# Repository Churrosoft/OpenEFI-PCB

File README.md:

# OpenEFI-PCB
Coleccion de PCB y planos recomendados para montar una OpenEFI

### Sobre el proyecto
OpenEFI es un ECU/EFI programable basada en arduino, totalmente OpenSource, fue creada originalmente para reemplazar una ecu existente en un motor naftero, pero tambien se puede usar para agregar inyeccion y/o encendido electronico a un motor antiguo, cuenta tambien con soporte para DTC's y autodiagnostico
* [OpenEFI](https://github.com/FDSoftware/OpenEFI) [Repo principal con todo el codigo]
* [OpenEFI-Tuner](https://github.com/FDSoftware/OpenEFI-Tuner) [Utilidad para revisar el estado de la ecu y modificarla]
* 
### Placas soportadas
* STM32F407xxxx: uEFI (v2/v3)
* STM32F103c8t6: OpenEFI (v0.5/v1/v2)

### coautores externos:
Dibujos:
Lucacik / ig: https://www.instagram.com/luca.cik/

si quieres usar otra placa basada en Arduino (Uno, Mega,DUE,etc), puedes hacerlo, pero los pcb no te serviran y capaz tengas que modificar ligeramente el codigo y el mapeo de los pines, proximamente agregare mas pcb ademas de mejorar los existentes

This source is distributed WITHOUT ANY EXPRESS OR IMPLIED WARRANTY, INCLUDING OF MERCHANTABILITY, SATISFACTORY QUALITY AND FITNESS FOR A PARTICULAR PURPOSE.

Please see LICENSE file for applicable conditions.

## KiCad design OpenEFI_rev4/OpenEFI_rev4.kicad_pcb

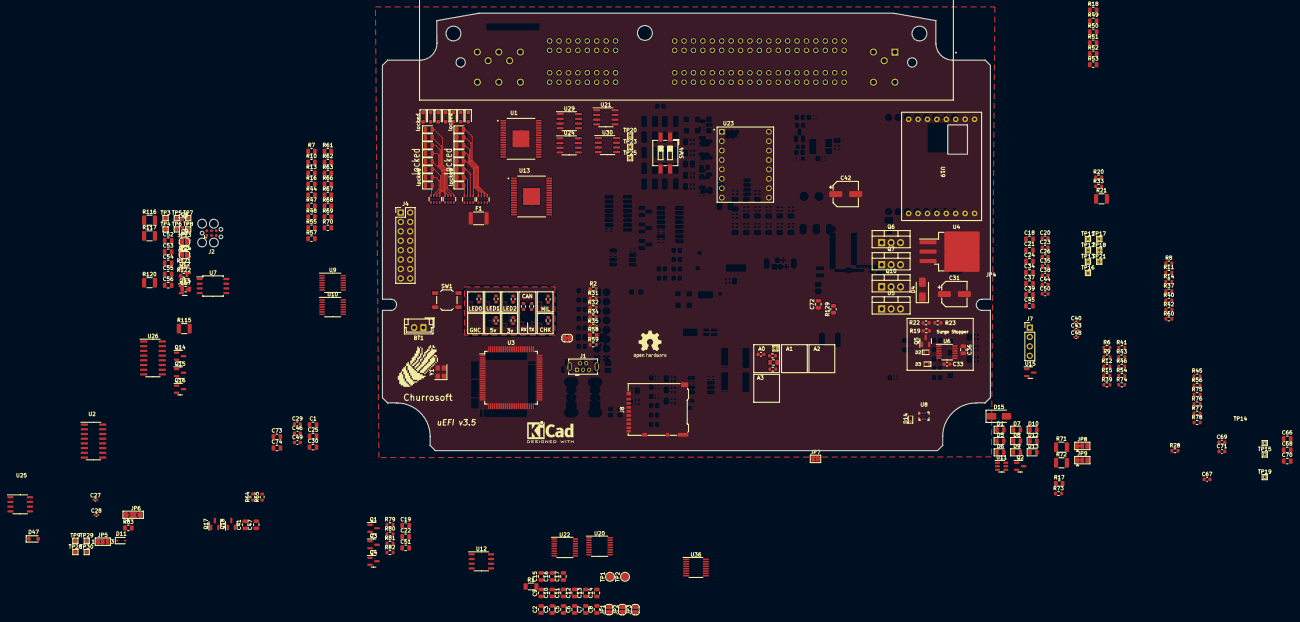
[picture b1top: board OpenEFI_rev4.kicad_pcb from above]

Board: 4 copper layers, 164.0 x 118.0 mm, 293 parts (0 on the bottom side), 205 nets.

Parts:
BT1: Battery_Cell; JST_EH_B2B-EH-A_1x02_P2.50mm_Vertical
C1, C5, C9, C10, C11, C12, C13, C14, C15, C17, C18, C21, C24, C25, C30, C32, C34, C36, C37, C39, C45, C66, C68, C70: 100nF; C_0805_2012Metric
C2, C3: 15pF; C_0805_2012Metric
C4, C20, C23, C26, C29, C35, C38, C44, C46, C49, C50, C67, C69, C71: 0.22uF; C_0603_1608Metric
C6, C73: 1uF; C_0805_2012Metric
C7, C8: 2.2uF; C_0805_2012Metric
C16: 4.7uF; C_0805_2012Metric
C19, C22, C41, C51, C52, C53, C54, C55, C56, C57, C72: 0.01uF; C_0805_2012Metric
C27, C28: 47p; C_0402_1005Metric
C31, C42: 100uF ±20% 35V; CP_Elec_6.3x7.7
C33: 47nF; C_0603_1608Metric
C40, C43: 1u; C_0402_1005Metric
C47: 4700pF; C_0805_2012Metric
C48: 100n; C_0402_1005Metric
C74: 0.1uF; C_0805_2012Metric
Churrosoft: SYM_Hot_Large; churro_new_v4
D1, D5, D6, D7, D8, D9, D10, D12, D13, D16, D17, D18, D19, D20, D21, D22, D43, D63, D65, D67, D69, D71, D73, D75, D77: LED; LED_0805_2012Metric
D2, D3: 1N4148; D_SOD-523
D4: SMAJ58CA; D_SMA
D11: MM3Z24VT1G; D_SOD-323
D14: 1N914WT; D_SOD-523
D15: SS26; D_SMA
D47, D64, D66, D68, D70, D72, D74, D76: D; D_SOD-323_HandSoldering
F1: Polyfuse; Fuse_1812_4532Metric
J1: USB_B; USB_Mini-B_Tensility_54-00023_Vertical
J2: Tag connect; Tag-Connect_TC2030-IDC-FP_2x03_P1.27mm_Vertical
J4: Conn_02x08_Odd_Even; PinHeader_2x08_P2.54mm_Vertical
J6: 1241434-1; TE_1241434-1
J7: Conn_01x04; PinHeader_1x04_P2.54mm_Vertical
J8: Micro_SD_Card_Det1; microSD_HC_Hirose_DM3AT-SF-PEJM5
JP1, JP2, JP3, JP23, JP24: SolderJumper_2_Open; SolderJumper-2_P1.3mm_Open_RoundedPad1.0x1.5mm
JP4: Jumper_NO_Small; SolderJumper-2_P1.3mm_Open_RoundedPad1.0x1.5mm
JP5: SolderJumper-3_P1.3mm_Bridged2Bar12_Pad1.0x1.5mm_NumberLabe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
JP6: SolderJumper_3_Bridged12; SolderJumper-3_P2.0mm_Open_TrianglePad1.0x1.5mm
JP7: Jumper_2_Open; SolderJumper-2_P1.3mm_Bridged2Bar_Pad1.0x1.5mm
JP8, JP9: Jumper_3_Bridged12; SolderJumper-3_P1.3mm_Bridged12_Pad1.0x1.5mm
LOGO1: Logo_Open_Hardware_Large; OSHW-Logo2_9.8x8mm_SilkScreen
Q1, Q2, Q3, Q4, Q12, Q13, Q14, Q15, Q16, Q17, Q18: AO3400A; SOT-23
Q5, Q8, Q9, Q11: SS8050; SOT-23
Q6, Q7: IRLZ44N; TO-220-3_Vertical
Q10: IRF540N; TO-220-3_Vertical
R1: 120R; R_1206_3216Metric
R2, R59, R121, R122: 10k; R_0603_1608Metric
R3, R4, R5, R24, R25, R26, R27, R29, R30: 4.7k; R_0603_1608Metric
R6, R9, R12, R15, R36, R39, R41, R43, R46, R54, R74: 2.49k +-1%; R_0603_1608Metric
R7, R44, R48, R61, R63, R66, R69, R70: 348k; R_0805_2012Metric
R8, R11, R14, R37, R38, R40, R42, R45, R56, R60, R75, R76, R77, R78: 470R; R_0603_1608Metric
R10, R13, R47, R55, R57, R62, R67, R68: 180k; R_0805_2012Metric
R16: 604R; R_0805_2012Metric
R17, R18, R49, R50, R51, R52, R53, R58, R83, R129: 10k; R_0805_2012Metric
R19: 1M 1/10W; R_0603_1608Metric
R20, R33, R73: 10R 1/10W; R_0603_1608Metric
R21: 0.01R; R_1210_3225Metric
R22: 57.6K 1/10W; R_0603_1608Metric
R23: 4.99K 1/10W; R_0603_1608Metric
R28: 3.88k; R_0603_1608Metric
R31, R32, R34, R64, R65, R79, R80, R81, R82: 1k; R_0603_1608Metric
R35: 100k; R_0603_1608Metric
R71, R72, R116, R117: 10K 1/2W; R_1210_3225Metric
R115, R120: 4.99K 1/2W; R_1210_3225Metric
RN1, RN2, RN3, RN4: 1k; R_Array_Convex_4x0603
SW1: SW_Push; SW_SPST_TL3342
SW4: SW_DIP_x02; SW_DIP_SPSTx02_Slide_6.7x6.64mm_W8.61mm_P2.54mm_LowProfile
SYM1: SYM_Hot_Small; KiCad-Logo2_5mm_SilkScreen
TP1: BOOT0; TestPoint_Pad_D2.0mm
TP2: BOOT1; TestPoint_Pad_D2.0mm
TP3, TP4, TP5, TP6, TP7, TP8, TP9, TP28, TP29, TP30: TestPoint; TestPoint_Pad_1.0x1.0mm
TP10, TP11, TP12, TP13, TP14, TP15, TP16, TP17, TP18, TP19, TP20, TP21, TP23, TP25: TestPoint_Alt; TestPoint_THTPad_1.0x1.0mm_Drill0.5mm
U1, U13: MCZ33810EK; SOP65P1030X245-33N
U2: 74HC4851; SOIC-16_3.9x9.9mm_P1.27mm
U3: STM32F407VGTx; LQFP-100_14x14mm_P0.5mm
U4: MIC2940A-3.3WU; TO-263-3_TabPin2
U5: MIC2940A-5.0WT; TO-220-3_Vertical
U6: LT4363IMS; MSOP-12_3x4mm_P0.65mm
U7: 25LCxxx; SOIC-8_5.275x5.275mm_P1.27mm
U8: BMP280; Bosch_LGA-8_2x2.5mm_P0.65mm_ClockwisePinNumbering
U9, U10: LMV324; TSSOP-14_4.4x5mm_P0.65mm
U11: SRV05-4; SOT-23-6
U12, U25: TJA1051T-3; SOP-8_3.9x4.9mm_P1.27mm
U15: REF3033; SOT-23
U19: f042_wideband_module; rusEFI_WBO
U20, U22: TPL7407LAPWR; TSSOP-16_4.4x5mm_P0.65mm
U21, U24, U29, U30: TC4424A; SOIC-8_3.9x4.9mm_P1.27mm
U23: PaP_Driver_v1; MODULE_A4988_STEPPER_MOTOR_DRIVER_CARRIER
U26: SP720ABTG; SOP-16_3.9x9.9mm_P1.27mm
U36: MAX9926UAEE+; QSOP-16_3.9x4.9mm_P0.635mm
Y1: 25MHz; Crystal_SMD_3225-4Pin_3.2x2.5mm

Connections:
5V_ENABLE: R33.1, U3.16 (PC1)
+3V3: C5.1, C6.1, C10.1, C11.1, C12.1, C13.1, C14.1, C15.1, C16.1, C17.1, C31.1, D1.2 (A), D5.2 (A), D7.2 (A), D8.2 (A), D9.2 (A), D10.2 (A), D12.2 (A), D13.2 (A), D14.2 (A), J2.1, J4.1, JP1.1 (A), JP2.1 (A), JP3.1 (A), JP5.2 (C), Q1.1 (G), Q2.1 (G), Q3.1 (G), Q4.1 (G), Q14.1 (G), Q15.1 (G), Q16.1 (G), Q17.1 (G), Q18.1 (G), R49.2, R51.2, R53.2, R59.1, R64.1, R65.1, R79.2, R80.2, R81.2, R82.2, R121.1, R122.1, U1.8 (VDD), U3.11 (VDD), U3.19 (VDD), U3.21 (VREF+), U3.28 (VDD), U3.50 (VDD), U3.75 (VDD), U3.100 (VDD), U4.3 (OUT), U7.3 (~WP), U7.7 (~HOLD), U7.8 (VCC), U8.6 (VDDIO), U8.8 (VDD), U9.4 (V+), U10.4 (V+), U12.5 (VIO), U13.8 (VDD), U23.5 (RESET), U23.6 (SLEEP), U26.16 (V+)
+5C: C40.1, D6.2 (A), D15.1 (K), F1.1, J4.2, Q10.3 (S), R6.2, R9.2, R12.2, R15.2, R18.1, R36.2, R39.2, R41.2, R43.2, R46.2, R50.1, R52.1, R54.2, R74.2, U2.16 (Vdd), U5.3 (OUT), U12.3 (VCC), U15.1 (IN), U19.1 (5V), U25.3 (VCC), U36.14 (VCC)
+12V: C42.1, JP4.2, JP6.3 (B), R21.1, R22.1, R28.2, R35.1, RN1.5 (R4.2), RN1.6 (R3.2), RN1.7 (R2.2), RN1.8 (R1.2), RN2.5 (R4.2), RN2.6 (R3.2), RN2.7 (R2.2), RN2.8 (R1.2), U1.25 (VPWR), U4.1 (IN), U5.1 (IN), U6.2 (OUT), U13.25 (VPWR), U20.9 (COM), U22.9 (COM), U23.16 (VMOT)
+12VA: D2.2 (A), JP4.1, Q5.2 (E), Q6.3 (S)
/ACC_DET: R58.1, U3.80 (PC12)
/AUX_CS_1: J4.3, U3.45 (PE14)
/AUX_CS_2: J4.5, U3.46 (PE15)
/AUX_IN_1: J4.7, U3.91 (PB5)
/AUX_IN_2: J4.9, U3.92 (PB6)
/AUX_IN_3: J4.11, U3.93 (PB7)
/AUX_IN_4: J4.13, U3.95 (PB8)
/AUX_OUT_1: J4.10, U3.33 (PC4)
/AUX_OUT_2: J4.12, U3.34 (PC5)
/AUX_OUT_3: J4.14, U3.35 (PB0)
/CHK: Q9.3 (C), R30.2
/CHK_OUT: R32.1, U3.66 (PC9), U20.6 (IN6)
/CKP: C41.1, C47.1, Q18.2 (S), R65.2, R122.2, TP7.1, U3.63 (PC6), U36.5 (COUT2)
/CKP/CMP_sensors/CKP_VR: C55.1, JP9.1 (A), R117.1
/CKP/CMP_sensors/IN1+: C54.1, R72.2, R115.1, TP4.1, U36.16 (IN1+)
/CKP/CMP_sensors/IN1-: C54.2, JP23.1 (A), R71.2, TP5.1, U36.15 (IN1-)
/CKP/CMP_sensors/IN2+: C57.2, JP24.1 (A), R117.2, TP6.1, U36.10 (IN2-)
/CKP/CMP_sensors/IN2-: C57.1, R116.2, R120.1, TP3.1, U36.9 (IN2+)
/CMP: Q17.2 (S), R64.2, R121.2, TP8.1, U3.64 (PC7), U36.4 (COUT1)
/ECN1: U1.24 (GIN0), U3.57 (PD10)
/ECN2: U1.23 (GIN1), U3.58 (PD11)
/INY1: U1.10 (DIN0), U3.55 (PD8)
/INY2: U1.11 (DIN1), U3.56 (PD9)
/LED0: R25.2, U3.7 (PC13)
/LED1: R26.2, U3.8 (PC14)
/LED2: R27.2, U3.9 (PC15)
/LED_CAN_RX: R24.2, U3.87 (PD6)
/LED_CAN_TX: R5.2, U3.88 (PD7)
/MEMORY_CS: TP9.1, U3.44 (PE13), U7.1 (~CS)
/MIL: Q8.3 (C), R29.2
/MIL_OUT: R31.1, U3.65 (PC8), U20.7 (IN7)
/MTR_DIR: U3.39 (PE8), U23.8 (DIR)
/MTR_ENABLE: U3.41 (PE10), U23.1 (ENABLE)
/MTR_FAULT: JP5.3 (B), U3.40 (PE9)
/MTR_STEP: U3.38 (PE7), U23.7 (STEP)
/MUX_A: Q16.2 (S), R49.1, U3.83 (PD2)
/MUX_B: Q14.2 (S), R51.1, U3.84 (PD3)
/MUX_C: Q15.2 (S), R53.1, U3.85 (PD4)
/NRST: C9.2, J2.3, SW1.1, U3.14 (NRST)
/PMIC1_CS: U1.4 (~CS), U3.78 (PC10)
/PMIC1_ENABLE: R83.2, R129.2, U1.9 (~OUTEN), U3.51 (PB12)
/PMIC2_CS: U3.79 (PC11), U13.4 (~CS)
/PMIC2_ENABLE: U3.52 (PB13), U13.9 (~OUTEN)
/PMIC/FB0: U1.2 (FB0), U13.2 (FB0)
/PMIC/FB1: U1.15 (FB1), U13.15 (FB1)
/PMIC/FB2: U1.31 (FB2), U13.31 (FB2)
/PMIC/FB3: U1.18 (FB3), U13.18 (FB3)
/PMIC/GD0: U1.3 (GD0), U13.3 (GD0), U21.2 (IN_A), U29.2 (IN_A)
/PMIC/GD1: U1.14 (GD1), U13.14 (GD1), U21.4 (IN_B), U29.4 (IN_B)
/PMIC/GD2: U1.30 (GD2), U13.30 (GD2), U24.2 (IN_A), U30.2 (IN_A)
/PMIC/GD3: U1.19 (GD3), U13.19 (GD3), U24.4 (IN_B), U30.4 (IN_B)
/RPM_OUT: R34.1, U3.42 (PE11)
/R_AAC: U3.3 (PE4), U22.1 (IN1), U22.2 (IN2)
/R_ECN_INY: U3.1 (PE2), U22.5 (IN5), U22.6 (IN6)
/R_GNC_GLP: U3.2 (PE3), U22.3 (IN3), U22.4 (IN4)
/R_LMB: U3.97 (PE0), U22.7 (IN7)
/SPI2_MISO: J4.6, J7.3, TP30.1, U1.7 (SO), U3.53 (PB14), U7.2 (MISO), U13.7 (SO)
/SPI2_MOSI: J4.8, J7.2, TP29.1, U1.6 (SI), U3.54 (PB15), U7.5 (MOSI), U13.6 (SI)
/SPI2_SCK: J4.4, J7.1, TP28.1, U1.5 (SCLK), U3.47 (PB10), U7.6 (SCK), U13.5 (SCLK)
/SYS_SWCLK: J2.4, U3.76 (PA14)
/SYS_SWDIO: J2.2, U3.72 (PA13)
/SYS_SWO: J2.6, U3.89 (PB3)
/Sensores/A: Q16.3 (D), R18.2, U2.11 (A)
/Sensores/AUX_CH1: C4.1, R38.1, TP10.1, U26.1 (I1)
/Sensores/AUX_CH2: C20.1, R11.1, TP11.1, U26.2 (I2)
/Sensores/AUX_CH3: C23.1, R14.1, TP12.1, U26.3 (I3)
/Sensores/AUX_CH4: C26.1, R37.1, TP13.1, U26.4 (I4)
/Sensores/AUX_CH5: C35.1, R8.1, TP16.1, U26.5 (I5)
/Sensores/AUX_CH6: C38.1, R60.1, TP17.1, U26.6 (I6)
/Sensores/AUX_CH7: C44.1, R42.1, TP18.1, U26.7 (I7)
/Sensores/AUX_CH8: C50.1, R40.1, TP21.1, U26.9 (I8)
/Sensores/B: Q14.3 (D), R50.2, U2.10 (B)
/Sensores/C: Q15.3 (D), R52.2, U2.9 (C)
/Sensores/CAN_RX: U19.5 (CAN_RX), U25.4 (RXD)
/Sensores/CAN_TX: U19.6 (CAN_TX), U25.1 (TXD)
/Sensores/CH_CLT: C69.1, R45.1, TP15.1, U26.14 (I13)
/Sensores/CH_IAT: C67.1, R47.2, R75.1, TP14.1, U26.15 (I14)
/Sensores/CH_MAP: C46.1, R13.2, R77.1, TP23.1, U26.11 (I10)
/Sensores/CH_O2: C49.1, R55.2, R78.1, TP25.1, U26.10 (I9)
/Sensores/CH_TPS: C71.1, R10.2, R76.1, TP19.1, U26.12 (I11)
/Sensores/CH_VBATT: C29.1, R56.1, R62.2, R67.2, TP20.1, U26.13 (I12)
/Sensores/LSU_Heater-: U19.11 (HEATER-), U19.12 (HEATER-)
/Sensores/mux_out: R57.2, U2.3 (OUT)
/TIM9_CH1: U3.4 (PE5), U20.1 (IN1), U20.2 (IN2), U20.3 (IN3)
/TIM9_CH2: U3.5 (PE6), U20.4 (IN4), U20.5 (IN5)
/USB_D+: J1.3 (D+), U3.71 (PA12), U11.3 (IO2)
/USB_D-: J1.2 (D-), U3.70 (PA11), U11.1 (IO1)
/VBUS: D15.2 (A), J1.1 (VBUS), U3.68 (PA9), U11.5 (VP)
A1: D11.1 (K), Q12.3 (D)
B1: C18.1, C21.1, C24.1, C32.1, C34.1, C37.1, C39.1, C45.1, R6.1, R8.2, R9.1, R11.2, R12.1, R14.2, R15.1, R36.1, R37.2, R38.2, R39.1, R40.2, R41.1, R42.2, R43.1, R60.2
B4: U20.12 (OUT5), U20.13 (OUT4)
C4: U20.14 (OUT3), U20.15 (OUT2), U20.16 (OUT1)
CAN+: C27.2, R1.2, U12.7 (CANH), U25.7 (CANH)
CAN-: C28.1, JP7.1 (A), U12.6 (CANL), U25.6 (CANL)
CKP-: C56.1, R116.1
CMP-: C52.1, R71.1
D4: U22.11 (OUT6), U22.12 (OUT5)
E1: C30.1, C66.1, C68.1, C70.1, R45.2, R46.1, R54.1, R74.1, R75.2, R76.2, R77.2
G3: U22.13 (OUT4), U22.14 (OUT3)
GND: BT1.2 (-), C1.2, C2.2, C3.2, C4.2, C5.2, C6.2, C7.2, C8.2, C9.1, C10.2, C11.2, C12.2, C13.2, C14.2, C15.2, C16.2, C17.2, C18.2, C19.1, C20.2, C21.2, C22.1, C23.2, C24.2, C25.2, C26.2, C27.1, C28.2, C29.2, C30.2, C31.2, C32.2, C33.2, C34.2, C35.2, C36.2, C37.2, C38.2, C39.2, C40.2, C42.2, C43.2, C44.2, C45.2, C46.2, C48.2, C49.2, C50.2, C51.1, C52.2, C53.2, C55.2, C56.2, C66.2, C67.2, C68.2, C69.2, C70.2, C71.2, C72.1, C73.1, C74.2, D3.2 (A), D4.2 (A2), D11.2 (A), D16.1 (K), D17.1 (K), D18.1 (K), D19.1 (K), D20.1 (K), D21.1 (K), D22.1 (K), D77.1 (K), J1.4 (GND), J1.5 (Shield), J2.5, J4.15, J4.16, J7.4, Q8.2 (E), Q9.2 (E), Q11.2 (E), Q12.2 (S), Q13.2 (S), R2.2, R3.2, R4.2, R7.2, R16.1, R23.1, R44.2, R48.2, R61.2, R63.2, R66.2, R69.2, R70.2, R83.1, R129.1, SW1.2, SW4.1, SW4.2, U1.33 (GND), U2.6 (EN), U2.8 (GND), U3.10 (VSS), U3.20 (VSSA), U3.27 (VSS), U3.74 (VSS), U3.99 (VSS), U4.2 (GND), U5.2 (GND), U6.9 (GND), U7.4 (GND), U8.1 (GND), U8.7 (GND), U9.11 (V-), U10.11 (V-), U11.2 (VN), U12.2 (GND), U12.8 (S), U13.33 (GND), U15.3 (GND), U19.2 (GND), U19.9 (HEAT_GND), U19.10 (HEAT_GND2), U20.8 (GND), U21.3 (GND), U22.8 (GND), U23.9 (GND), U23.15 (GND), U24.3 (GND), U25.2 (GND), U25.8 (S), U26.8 (GND), U29.3 (GND), U30.3 (GND), U36.1 (INT_THRS1), U36.3 (BIAS1), U36.6 (BIAS2), U36.8 (INT_THRS2), U36.11 (GND), U36.13 (ZERO_EN), Y1.2, Y1.4
H1: Q13.3 (D), R59.2
H3: U22.15 (OUT2), U22.16 (OUT1)
IGN1: RN3.8 (R1.2), U21.7 (OUT_A), U29.7 (OUT_A)
IGN2: RN3.7 (R2.2), U21.5 (OUT_B), U29.5 (OUT_B)
IGN3: RN3.5 (R4.2), U24.7 (OUT_A), U30.7 (OUT_A)
IGN4: RN3.6 (R3.2), U24.5 (OUT_B), U30.5 (OUT_B)
IGN_V+: C73.2, C74.1, JP6.2 (C), U21.6 (VDD), U24.6 (VDD), U29.6 (VDD), U30.6 (VDD)
INJ1: D47.1 (K), U1.1 (OUT0), U13.1 (OUT0)
INJ2: D64.1 (K), U1.16 (OUT1), U13.16 (OUT1)
INJ3: D66.1 (K), U1.32 (OUT2), U13.32 (OUT2)
INJ4: D68.1 (K), U1.17 (OUT3), U13.17 (OUT3)
K1: C1.1, R78.2
MCU-D23: C19.2, C22.2, C51.2, C72.2, Q1.3 (D), Q2.3 (D), Q3.3 (D), Q4.3 (D), R79.1, R80.1, R81.1, R82.1
unnamed: BT1.1 (+), D14.1 (K), U3.6 (VBAT)
unnamed: C25.1, R16.2, R28.1, R56.2
unnamed: C41.2, SW4.4
unnamed: C47.2, SW4.3
unnamed: D1.1 (K), R5.1
unnamed: D2.1 (K), Q5.1 (B), R17.2
unnamed: D3.1 (K), R17.1
unnamed: D4.1 (A1), Q6.2 (D), Q7.2 (D), U6.5 (VCC)
unnamed: D5.1 (K), R24.1
unnamed: D6.1 (K), R4.1
unnamed: D7.1 (K), R3.1
unnamed: D8.1 (K), R25.1
unnamed: D9.1 (K), R26.1
unnamed: D10.1 (K), R27.1
unnamed: D12.1 (K), R29.1
unnamed: D13.1 (K), R30.1
unnamed: D16.2 (A), RN3.2 (R2.1)
unnamed: D17.2 (A), RN3.3 (R3.1)
unnamed: D18.2 (A), RN3.4 (R4.1)
unnamed: D19.2 (A), RN4.1 (R1.1)
unnamed: D20.2 (A), RN4.2 (R2.1)
unnamed: D21.2 (A), RN4.3 (R3.1)
unnamed: D22.2 (A), RN4.4 (R4.1)
unnamed: D43.2 (A), RN1.1 (R1.1)
unnamed: D43.1 (K), D47.2 (A)
unnamed: D63.2 (A), RN1.2 (R2.1)
unnamed: D63.1 (K), D64.2 (A)
unnamed: D65.2 (A), RN1.3 (R3.1)
unnamed: D65.1 (K), D66.2 (A)
unnamed: D67.2 (A), RN1.4 (R4.1)
unnamed: D67.1 (K), D68.2 (A)
unnamed: D69.2 (A), RN2.1 (R1.1)
unnamed: D69.1 (K), D70.2 (A)
unnamed: D71.2 (A), RN2.2 (R2.1)
unnamed: D71.1 (K), D72.2 (A)
unnamed: D73.2 (A), RN2.3 (R3.1)
unnamed: D73.1 (K), D74.2 (A)
unnamed: D75.2 (A), RN2.4 (R4.1)
unnamed: D75.1 (K), D76.2 (A)
unnamed: D77.2 (A), RN3.1 (R1.1)
unnamed: JP1.2 (B), U23.3 (M1)
unnamed: JP2.2 (B), U23.2 (M0)
unnamed: JP3.2 (B), U23.4 (M2)
unnamed: JP5.1 (A), U23.10 (FAULT)
unnamed: F1.2, JP6.1 (A)
unnamed: JP7.2 (B), R1.1
unnamed: C53.1, JP8.1 (A), R72.1
unnamed: JP8.3 (B), Q17.3 (D)
unnamed: JP9.3 (B), Q18.3 (D)
unnamed: JP23.2 (B), R115.2
unnamed: JP24.2 (B), R120.2
unnamed: Q5.3 (C), R19.2, R73.2
unnamed: Q6.1 (G), R73.1
unnamed: Q7.1 (G), R20.1
unnamed: Q7.3 (S), R21.2, U6.3 (SNS)
unnamed: Q8.1 (B), R31.2
unnamed: Q9.1 (B), R32.2
unnamed: Q10.1 (G), R33.2
unnamed: Q11.1 (B), R34.2
unnamed: Q11.3 (C), Q12.1 (G), R35.2
unnamed: Q13.1 (G), R58.2
unnamed: R2.1, TP1.1, U3.94 (BOOT0)
unnamed: TP2.1, U3.37 (PB2)
unnamed: C7.1, U3.49 (VCAP_1)
unnamed: C8.1, U3.73 (VCAP_2)
unnamed: R22.2, R23.2, U6.1 (FB)
unnamed: C33.1, R19.1, R20.2, U6.4 (GATE)
unnamed: C36.1, U6.12 (TMR)
unnamed: R47.1, R48.1, U9.3 (+)
unnamed: U9.1, U9.2 (-)
unnamed: R7.1, R10.1, U9.5 (+)
unnamed: U9.6 (-), U9.7
unnamed: R13.1, R44.1, U9.10 (+)
unnamed: U9.8, U9.9 (-)
unnamed: R62.1, R63.1, U9.12 (+)
unnamed: U9.13 (-), U9.14
unnamed: R55.1, R61.1, U10.3 (+)
unnamed: U10.1, U10.2 (-)
unnamed: R67.1, R69.1, U10.5 (+)
unnamed: U10.6 (-), U10.7
unnamed: R68.1, R70.1, U10.10 (+)
unnamed: U10.8, U10.9 (-)
unnamed: R57.1, R66.1, U10.12 (+)
unnamed: U10.13 (-), U10.14
OSC_IN: C2.1, U3.12 (PH0), Y1.1
OSC_OUT: C3.1, U3.13 (PH1), Y1.3
VDDA: C43.1, C48.1, U3.22 (VDDA), U15.2 (OUT)

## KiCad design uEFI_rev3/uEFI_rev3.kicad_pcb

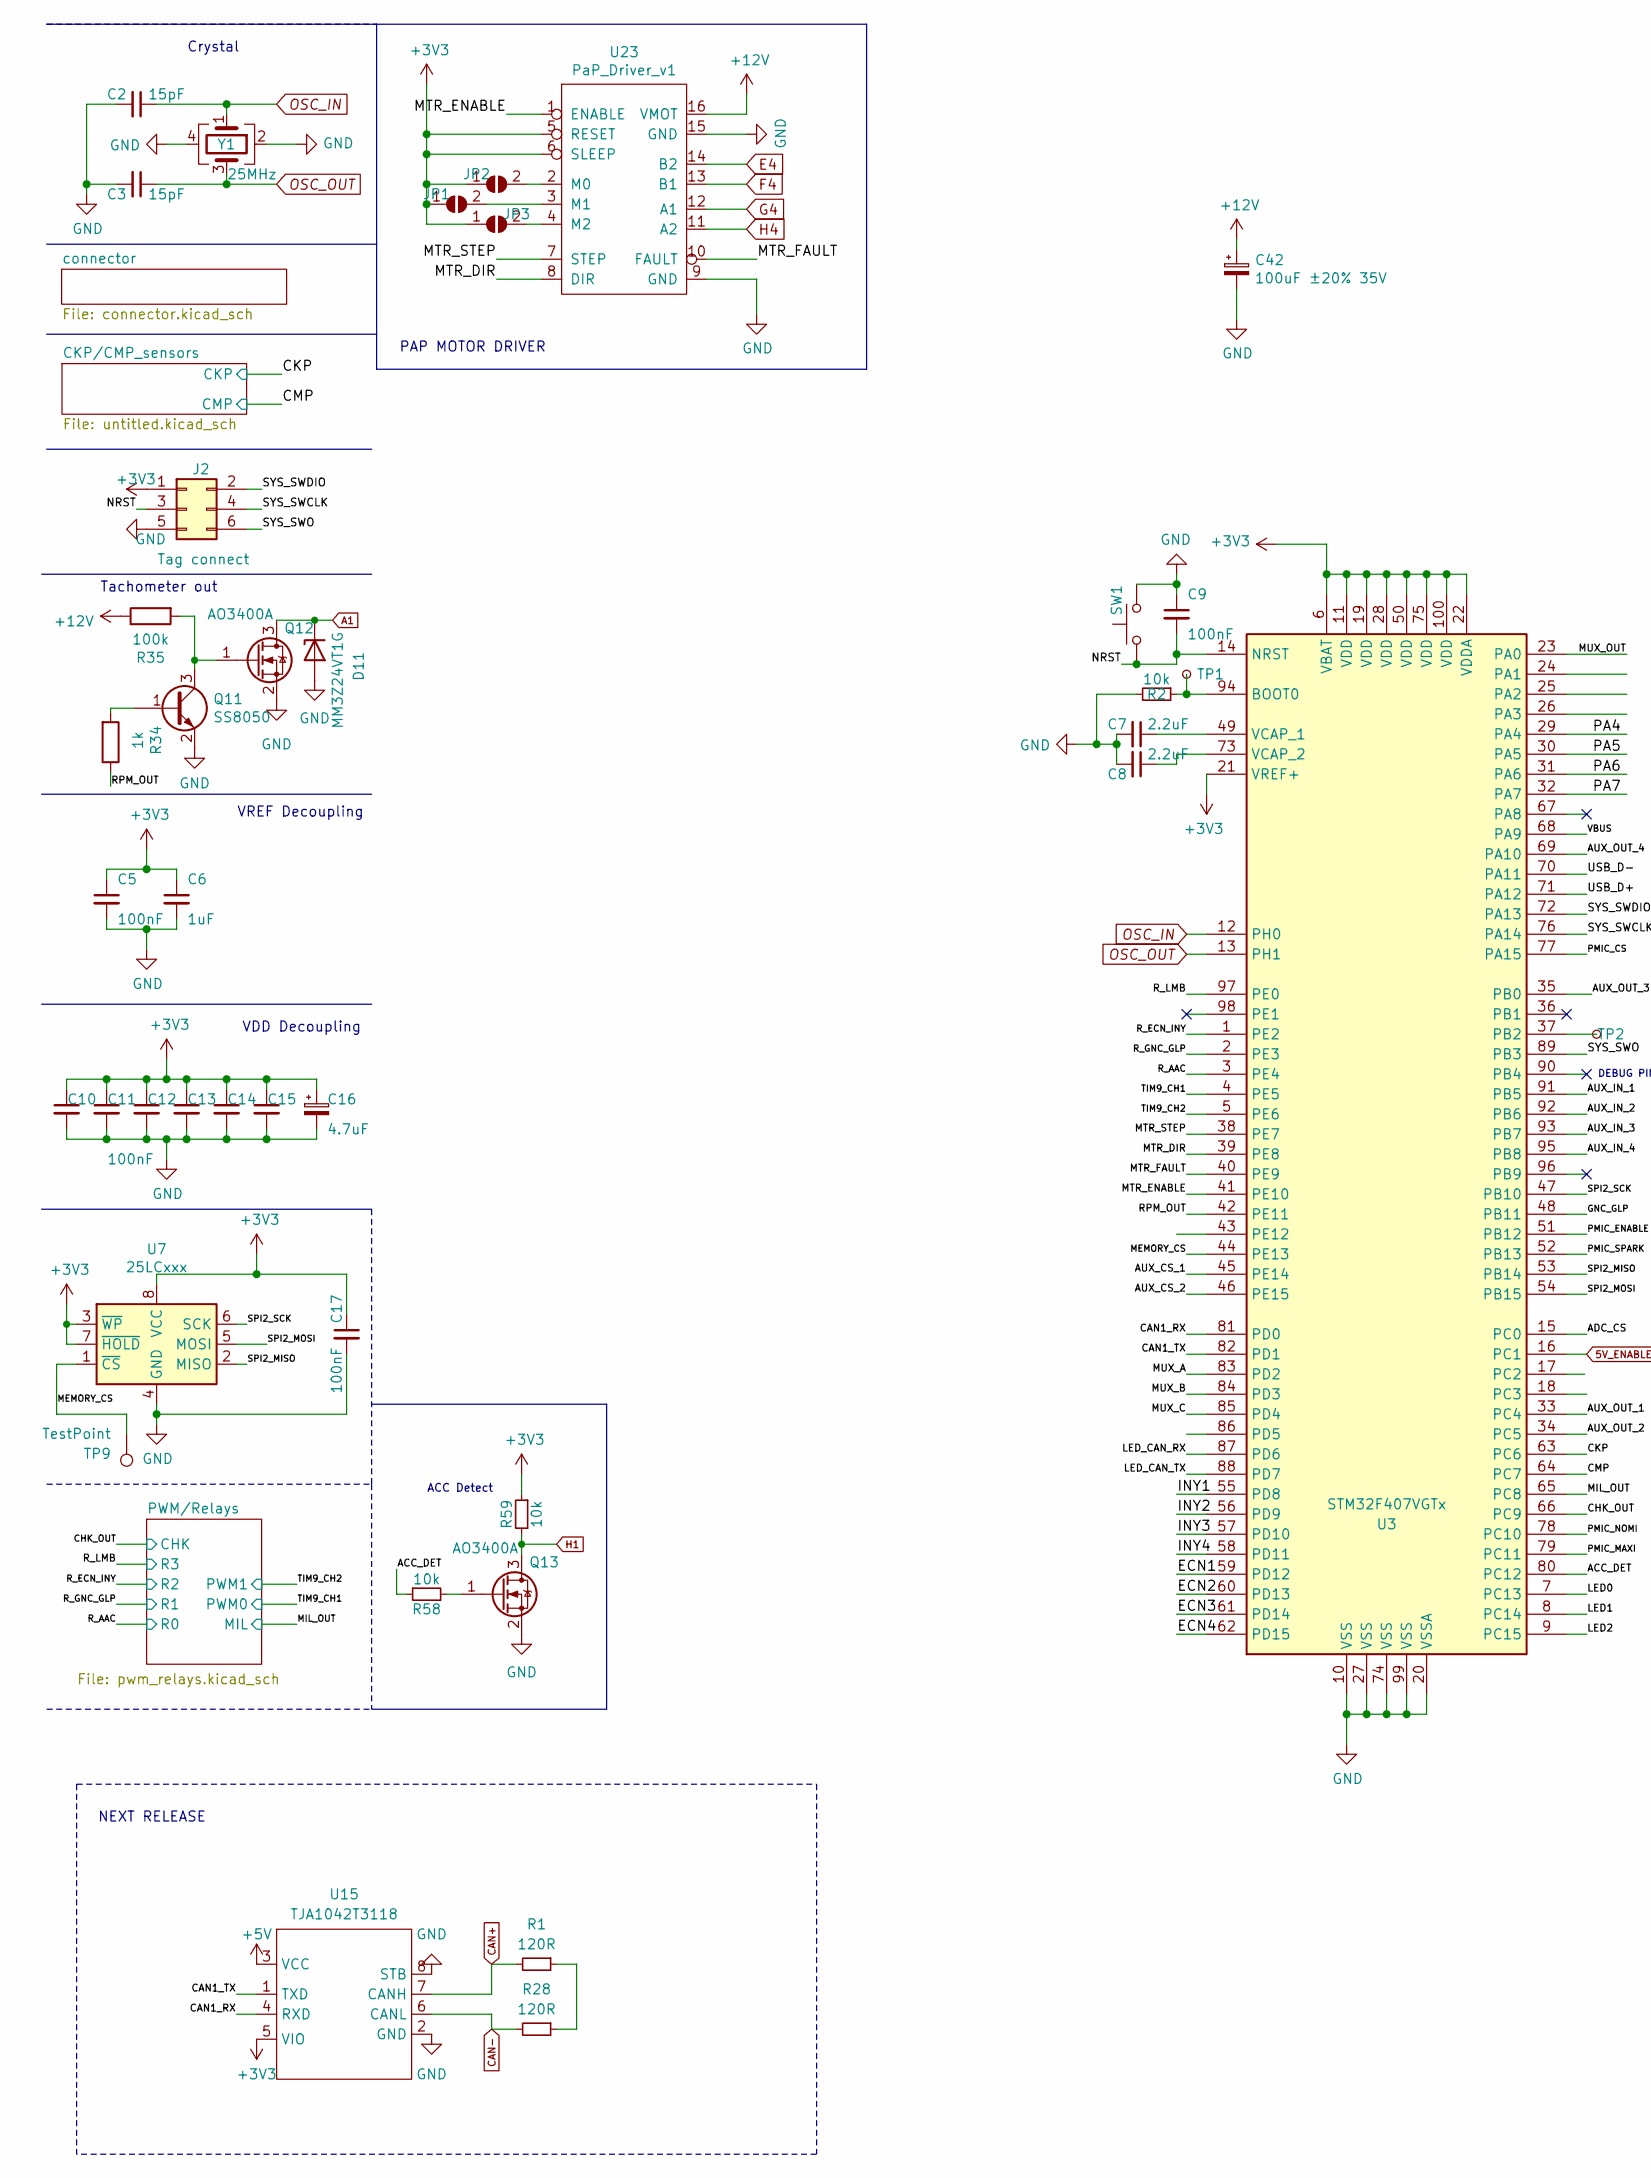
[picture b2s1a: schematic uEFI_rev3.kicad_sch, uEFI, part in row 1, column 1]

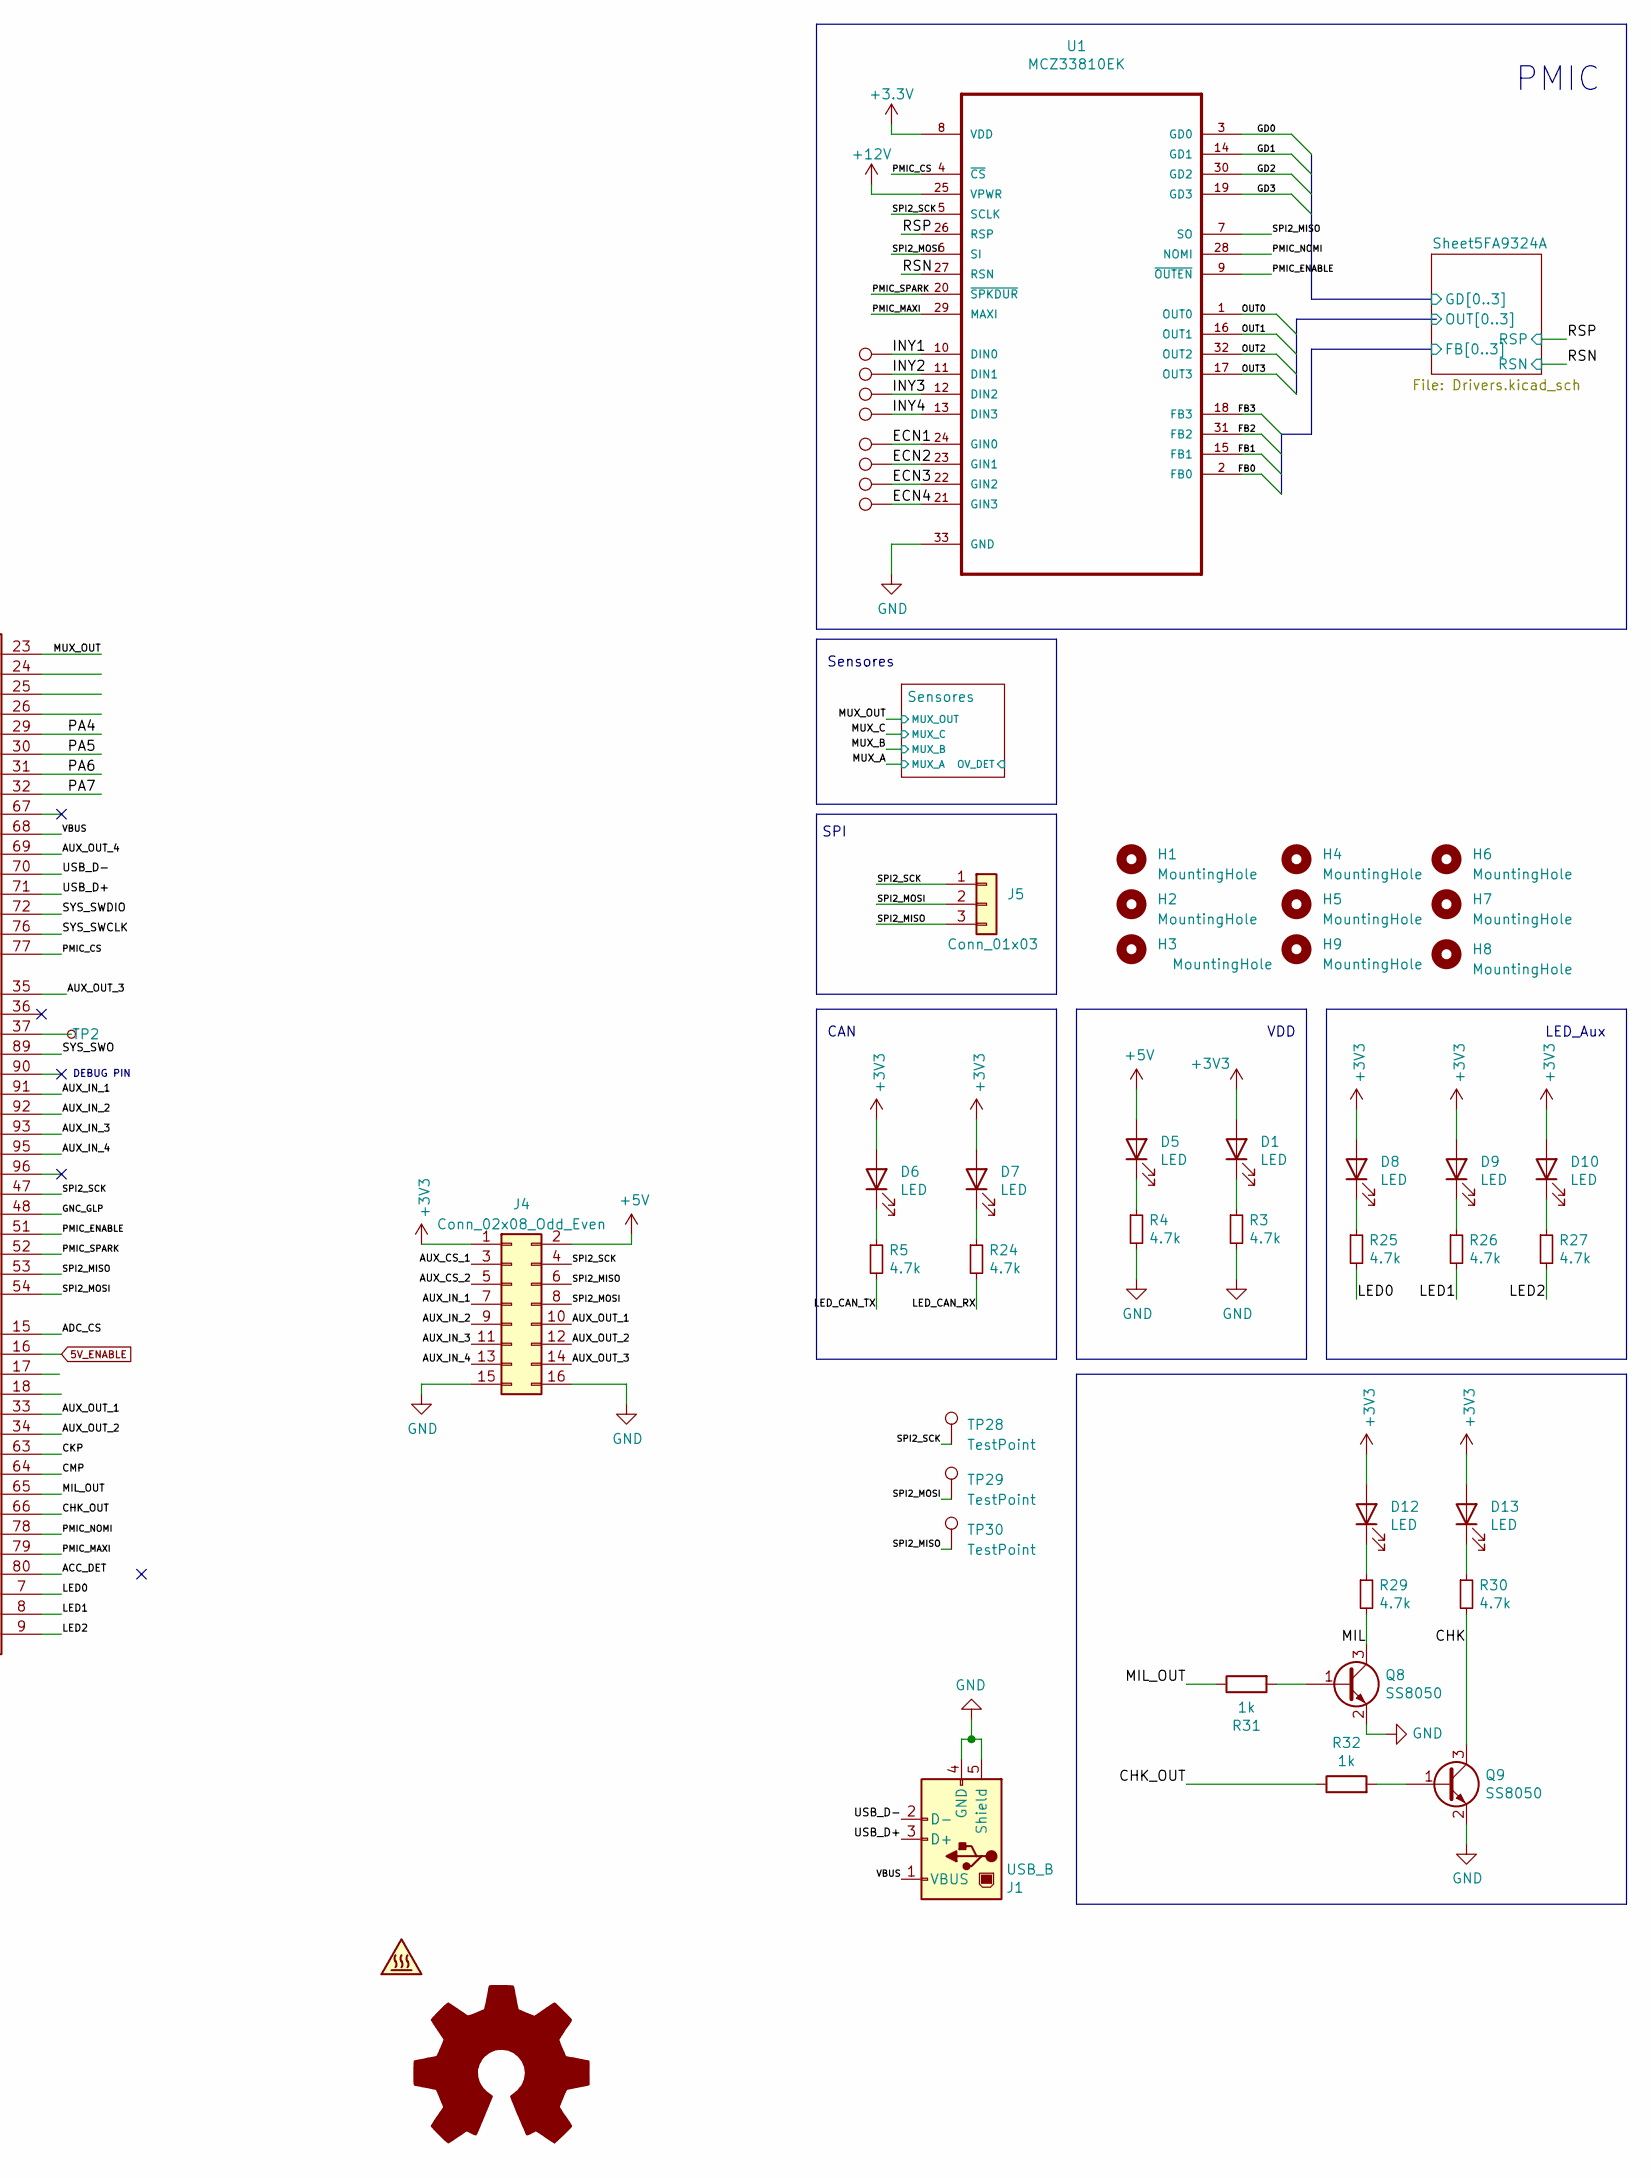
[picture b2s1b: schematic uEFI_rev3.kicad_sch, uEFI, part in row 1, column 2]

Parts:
C2, C3: 15pF; C_0805_2012Metric; LCSC C1794
C5, C9, C10, C11, C12, C13, C14, C15, C17: 100nF; C_0805_2012Metric; LCSC C49678
C6: 1uF; C_0805_2012Metric; LCSC C28323
C7, C8: 2.2uF; C_0805_2012Metric; LCSC C49217
C16: 4.7uF; C_0805_2012Metric; LCSC 0805
C42: 100uF ±20% 35V; CP_Elec_6.3x7.7; LCSC C141427
D1, D5, D6, D7, D8, D9, D10, D12, D13: LED; LED_0603_1608Metric
D11: MM3Z24VT1G; D_SOD-323
H1, H2, H3, H4, H9: MountingHole; MountingHole_2.2mm_M2_Pad_Via
H5, H6, H7, H8: MountingHole; TestPoint_Pad_D1.0mm
J1: USB_B; USB_B_OST_USB-B1HSxx_Horizontal
J2: Tag connect; Tag-Connect_TC2030-IDC-FP_2x03_P1.27mm_Vertical
J4: Conn_02x08_Odd_Even; PinHeader_2x08_P1.27mm_Vertical
J5: Conn_01x03; PinHeader_1x03_P2.54mm_Vertical
JP1, JP2, JP3: SolderJumper_2_Open; SolderJumper-2_P1.3mm_Open_RoundedPad1.0x1.5mm
LOGO1: Logo_Open_Hardware_Large; OSHW-Logo2_9.8x8mm_SilkScreen
Q8, Q9, Q11: SS8050; SOT-23; LCSC C2150
Q12, Q13: AO3400A; SOT-23; LCSC C347475
R1, R28: 120R; R_1206_3216Metric
R2, R58, R59: 10k; R_0603_1608Metric
R3, R4, R5, R24, R25, R26, R27, R29, R30: 4.7k; R_0603_1608Metric; LCSC C23162
R31, R32, R34: 1k; R_0603_1608Metric; LCSC C21190
R35: 100k; R_0603_1608Metric; LCSC ---
SW1: SW_Push; SW_SPST_TL3342
SYM1: SYM_Hot_Small; KiCad-Logo2_5mm_SilkScreen
TP1: BOOT0; TestPoint_Pad_D2.0mm
TP2: BOOT1; TestPoint_Pad_D2.0mm
TP9, TP20, TP21, TP22, TP23, TP24, TP25, TP26, TP27, TP28, TP29, TP30: TestPoint; TestPoint_Pad_1.0x1.0mm
U1: MCZ33810EK; SOP65P1030X245-33N
U3: STM32F407VGTx; LQFP-100_14x14mm_P0.5mm
U7: 25LCxxx; SOIC-8_5.275x5.275mm_P1.27mm
U15: TJA1042T3118; HTSOP-8-1EP_3.9x4.9mm_P1.27mm_EP2.4x3.2mm
U23: PaP_Driver_v1; IC_DRV8825_STEPPER_MOTOR_DRIVER_CARRIER
Y1: 25MHz; Crystal_SMD_3225-4Pin_3.2x2.5mm

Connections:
5V_ENABLE: U3.16 (PC1); also elsewhere on the board
+5C: D5.2 (A), J4.2, U15.3 (VCC); also elsewhere on the board
+12V: C42.1, R35.1, U1.25 (VPWR), U23.16 (VMOT); also elsewhere on the board
/ACC_DET: R58.1, U3.80 (PC12)
/ADC_CS: U3.15 (PC0)
/AUX_CS_1: J4.3, U3.45 (PE14)
/AUX_CS_2: J4.5, U3.46 (PE15)
/AUX_IN_1: J4.7, U3.91 (PB5)
/AUX_IN_2: J4.9, U3.92 (PB6)
/AUX_IN_3: J4.11, U3.93 (PB7)
/AUX_IN_4: J4.13, U3.95 (PB8)
/AUX_OUT_1: J4.10, U3.33 (PC4)
/AUX_OUT_2: J4.12, U3.34 (PC5)
/AUX_OUT_3: J4.14, U3.35 (PB0)
/AUX_OUT_4: U3.69 (PA10)
/CAN1_RX: U3.81 (PD0), U15.4 (RXD)
/CAN1_TX: U3.82 (PD1), U15.1 (TXD)
/CHK: Q9.3 (C), R30.2
/CHK_OUT: R32.1, U3.66 (PC9); also elsewhere on the board
/CKP: U3.63 (PC6); also elsewhere on the board
/CMP: U3.64 (PC7); also elsewhere on the board
/ECN1: TP24.1, U1.24 (GIN0), U3.59 (PD12)
/ECN2: TP25.1, U1.23 (GIN1), U3.60 (PD13)
/ECN3: TP26.1, U1.22 (GIN2), U3.61 (PD14)
/ECN4: TP27.1, U1.21 (GIN3), U3.62 (PD15)
/GNC_GLP: U3.48 (PB11)
/INY1: TP20.1, U1.10 (DIN0), U3.55 (PD8)
/INY2: TP21.1, U1.11 (DIN1), U3.56 (PD9)
/INY3: TP22.1, U1.12 (DIN2), U3.57 (PD10)
/INY4: TP23.1, U1.13 (DIN3), U3.58 (PD11)
/LED0: R25.2, U3.7 (PC13)
/LED1: R26.2, U3.8 (PC14)
/LED2: R27.2, U3.9 (PC15)
/LED_CAN_RX: R24.2, U3.87 (PD6)
/LED_CAN_TX: R5.2, U3.88 (PD7)
/MEMORY_CS: TP9.1, U3.44 (PE13), U7.1 (~CS)
/MIL: Q8.3 (C), R29.2
/MIL_OUT: R31.1, U3.65 (PC8); also elsewhere on the board
/MTR_DIR: U3.39 (PE8), U23.8 (DIR)
/MTR_ENABLE: U3.41 (PE10), U23.1 (ENABLE)
/MTR_FAULT: U3.40 (PE9), U23.10 (FAULT)
/MTR_STEP: U3.38 (PE7), U23.7 (STEP)
/MUX_A: U3.83 (PD2); also elsewhere on the board
/MUX_B: U3.84 (PD3); also elsewhere on the board
/MUX_C: U3.85 (PD4); also elsewhere on the board
/MUX_OUT: U3.23 (PA0); also elsewhere on the board
/NRST: C9.2, J2.3, SW1.1, U3.14 (NRST)
/PA4: U3.29 (PA4)
/PA5: U3.30 (PA5)
/PA6: U3.31 (PA6)
/PA7: U3.32 (PA7)
/PMIC_CS: U1.4 (~CS), U3.77 (PA15)
/PMIC_ENABLE: U1.9 (~OUTEN), U3.51 (PB12)
/PMIC_MAXI: U1.29 (MAXI), U3.79 (PC11)
/PMIC_NOMI: U1.28 (NOMI), U3.78 (PC10)
/PMIC_SPARK: U1.20 (~SPKDUR), U3.52 (PB13)
/RPM_OUT: R34.1, U3.42 (PE11)
/RSN: U1.27 (RSN); also elsewhere on the board
/RSP: U1.26 (RSP); also elsewhere on the board
/R_AAC: U3.3 (PE4); also elsewhere on the board
/R_ECN_INY: U3.1 (PE2); also elsewhere on the board
/R_GNC_GLP: U3.2 (PE3); also elsewhere on the board
/R_LMB: U3.97 (PE0); also elsewhere on the board
/SPI2_MISO: J4.6, J5.3, TP30.1, U1.7 (SO), U3.53 (PB14), U7.2 (MISO)
/SPI2_MOSI: J4.8, J5.2, TP29.1, U1.6 (SI), U3.54 (PB15), U7.5 (MOSI)
/SPI2_SCK: J4.4, J5.1, TP28.1, U1.5 (SCLK), U3.47 (PB10), U7.6 (SCK)
/SYS_SWCLK: J2.4, U3.76 (PA14)
/SYS_SWDIO: J2.2, U3.72 (PA13)
/SYS_SWO: J2.6, U3.89 (PB3)
/Sheet5FA9324A/FB0: U1.2 (FB0); also elsewhere on the board
/Sheet5FA9324A/FB1: U1.15 (FB1); also elsewhere on the board
/Sheet5FA9324A/FB2: U1.31 (FB2); also elsewhere on the board
/Sheet5FA9324A/FB3: U1.18 (FB3); also elsewhere on the board
/Sheet5FA9324A/GD0: U1.3 (GD0); also elsewhere on the board
/Sheet5FA9324A/GD1: U1.14 (GD1); also elsewhere on the board
/Sheet5FA9324A/GD2: U1.30 (GD2); also elsewhere on the board
/Sheet5FA9324A/GD3: U1.19 (GD3); also elsewhere on the board
/TIM9_CH1: U3.4 (PE5); also elsewhere on the board
/TIM9_CH2: U3.5 (PE6); also elsewhere on the board
/USB_D+: J1.3 (D+), U3.71 (PA12)
/USB_D-: J1.2 (D-), U3.70 (PA11)
/VBUS: J1.1 (VBUS), U3.68 (PA9)
A1: D11.1 (K), Q12.3 (D); also elsewhere on the board
CAN+: R1.2, U15.7 (CANH); also elsewhere on the board
CAN-: R28.2, U15.6 (CANL); also elsewhere on the board
E4: U23.14 (B2); also elsewhere on the board
F4: U23.13 (B1); also elsewhere on the board
G4: U23.12 (A1); also elsewhere on the board
GND: C2.2, C3.2, C5.2, C6.2, C7.2, C8.2, C9.1, C10.2, C11.2, C12.2, C13.2, C14.2, C15.2, C16.2, C17.2, C42.2, D11.2 (A), J1.4 (GND), J1.5 (Shield), J2.5, J4.15, J4.16, Q8.2 (E), Q9.2 (E), Q11.2 (E), Q12.2 (S), Q13.2 (S), R2.2, R3.2, R4.2, SW1.2, U1.33 (GND), U3.10 (VSS), U3.20 (VSSA), U3.27 (VSS), U3.74 (VSS), U3.99 (VSS), U7.4 (GND), U15.2 (GND), U15.8 (STB), U23.9 (GND), U23.15 (GND), Y1.2, Y1.4; also elsewhere on the board
H1: Q13.3 (D), R59.2; also elsewhere on the board
H4: U23.11 (A2); also elsewhere on the board
L3: U1.17 (OUT3); also elsewhere on the board
L4: U1.32 (OUT2); also elsewhere on the board
M3: U1.16 (OUT1); also elsewhere on the board
M4: U1.1 (OUT0); also elsewhere on the board
unnamed: C7.1, U3.49 (VCAP_1)
unnamed: C8.1, U3.73 (VCAP_2)
unnamed: D1.1 (K), R3.1
unnamed: D5.1 (K), R4.1
unnamed: D6.1 (K), R5.1
unnamed: D7.1 (K), R24.1
unnamed: D8.1 (K), R25.1
unnamed: D9.1 (K), R26.1
unnamed: D10.1 (K), R27.1
unnamed: D12.1 (K), R29.1
unnamed: D13.1 (K), R30.1
unnamed: JP1.2 (B), U23.3 (M1)
unnamed: JP2.2 (B), U23.2 (M0)
unnamed: JP3.2 (B), U23.4 (M2)
unnamed: Q8.1 (B), R31.2
unnamed: Q9.1 (B), R32.2
unnamed: Q11.1 (B), R34.2
unnamed: Q11.3 (C), Q12.1 (G), R35.2
unnamed: Q13.1 (G), R58.2
unnamed: R1.1, R28.1
unnamed: R2.1, TP1.1, U3.94 (BOOT0)
unnamed: TP2.1, U3.37 (PB2)
OSC_IN: C2.1, U3.12 (PH0), Y1.1
OSC_OUT: C3.1, U3.13 (PH1), Y1.3

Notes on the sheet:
Sensores
DEBUG PIN
CAN
ACC Detect
Crystal
NEXT RELEASE
VDD
VREF Decoupling
PMIC
VDD Decoupling
LED_Aux
SPI
PAP MOTOR DRIVER
Tachometer out

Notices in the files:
OpenEFI_rev4/Drivers.kicad_sch:
MIT Licence
OpenEFI_rev4/connector.kicad_sch:
CERN-OHL-S Licence
